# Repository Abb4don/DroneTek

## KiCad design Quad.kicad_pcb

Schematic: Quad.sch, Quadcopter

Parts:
C1, C4: 1uF
C2, C3: 22pF
CON1: USB-MINI-B
CON2: AVR-ISP-6
P1, P2: MPU6050
P3: nRF24l01
P4: CONN_2
R1, R2: 22
R3, R4: 100
U1: TC1017; SOT-23-5
X1: CRYSTAL
adaprog1: ADAPROG_ATMEGA32U4

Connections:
3V3: C1.1, P1.1, P2.1, P3.1, U1.5 (OUT)
GND: C1.2, C2.1, C3.1, C4.1, CON1.5 (GND), CON1.6 (SHELL1), CON1.7 (SHELL2), CON1.8 (SHELL3), CON1.9 (SHELL4), CON2.6, P1.4, P2.4, P3.8, P4.2 (PM), U1.2 (GND), adaprog1.5 (UGND), adaprog1.15 (GND), adaprog1.23 (GND1), adaprog1.35 (GND2), adaprog1.43 (GND3)
unnamed: C4.2, adaprog1.6 (UCAP)
unnamed: P1.2, R4.2
unnamed: P1.3, R3.2
unnamed: R4.1, adaprog1.18 (PD0(INT0/OC0B/SCL))
unnamed: R3.1, adaprog1.19 (PD1(INT1/SDA))
unnamed: CON1.2 (D-), R1.1
unnamed: R2.2, adaprog1.4 (D+)
unnamed: CON1.3 (D+), R2.1
unnamed: C2.2, X1.2, adaprog1.17 (XTAL1)
unnamed: C3.2, X1.1, adaprog1.16 (XTAL2)
unnamed: CON1.1 (VBUS), adaprog1.7 (VBUS)
unnamed: R1.2, adaprog1.3 (D-)
VCC: CON2.2, P4.1, U1.1 (IN), U1.3 (~EN~), adaprog1.2 (UVCC), adaprog1.14 (VCC), adaprog1.24 (AVCC), adaprog1.34 (VCC1), adaprog1.44 (AVCC1)
ce: P3.2, adaprog1.12 (PB7(OC0A/OC1C/RTS))
csn: P3.3, adaprog1.8 (PB0(SS))
irq: P3.7, adaprog1.25 (PD4(ICP1/ADC8))
miso: CON2.1, P3.6, adaprog1.11 (PB3(PDO/MISO))
mosi: CON2.4, P3.5, adaprog1.10 (PB2(PDI/MOSI))
rst: CON2.5, adaprog1.13 (/RESET)
sck: CON2.3, P3.4, adaprog1.9 (PB1(SCK))

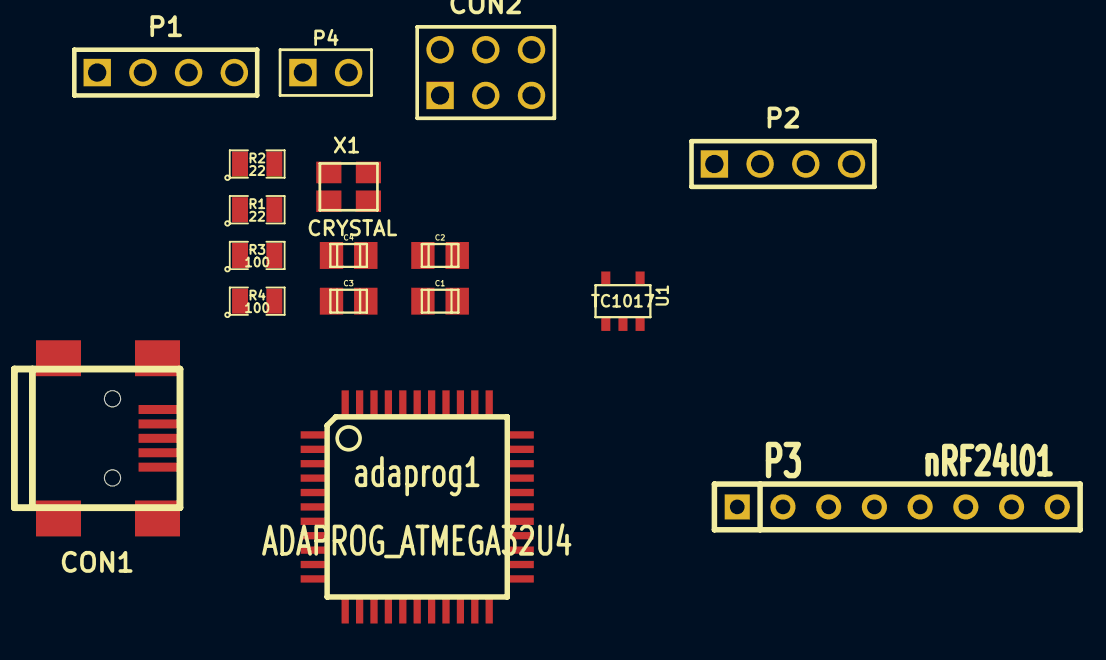
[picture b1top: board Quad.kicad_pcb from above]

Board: 2 copper layers, 17 parts (0 on the bottom side), 22 nets, no tracks yet.

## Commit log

2014-05-11 added pcb first version
